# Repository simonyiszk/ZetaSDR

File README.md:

# ZetaSDR
ZetaSDR HF rádióvevő extra funkciókkal kiegészítve (PLL, USB hangkártya)

Fejlesztői környezet: [https://github.com/Community-PIO-CH32V/platform-ch32v](https://github.com/Community-PIO-CH32V/platform-ch32v).\
Az elektronikai terveket [KiCad](https://www.kicad.org/) seítségével készítettem.

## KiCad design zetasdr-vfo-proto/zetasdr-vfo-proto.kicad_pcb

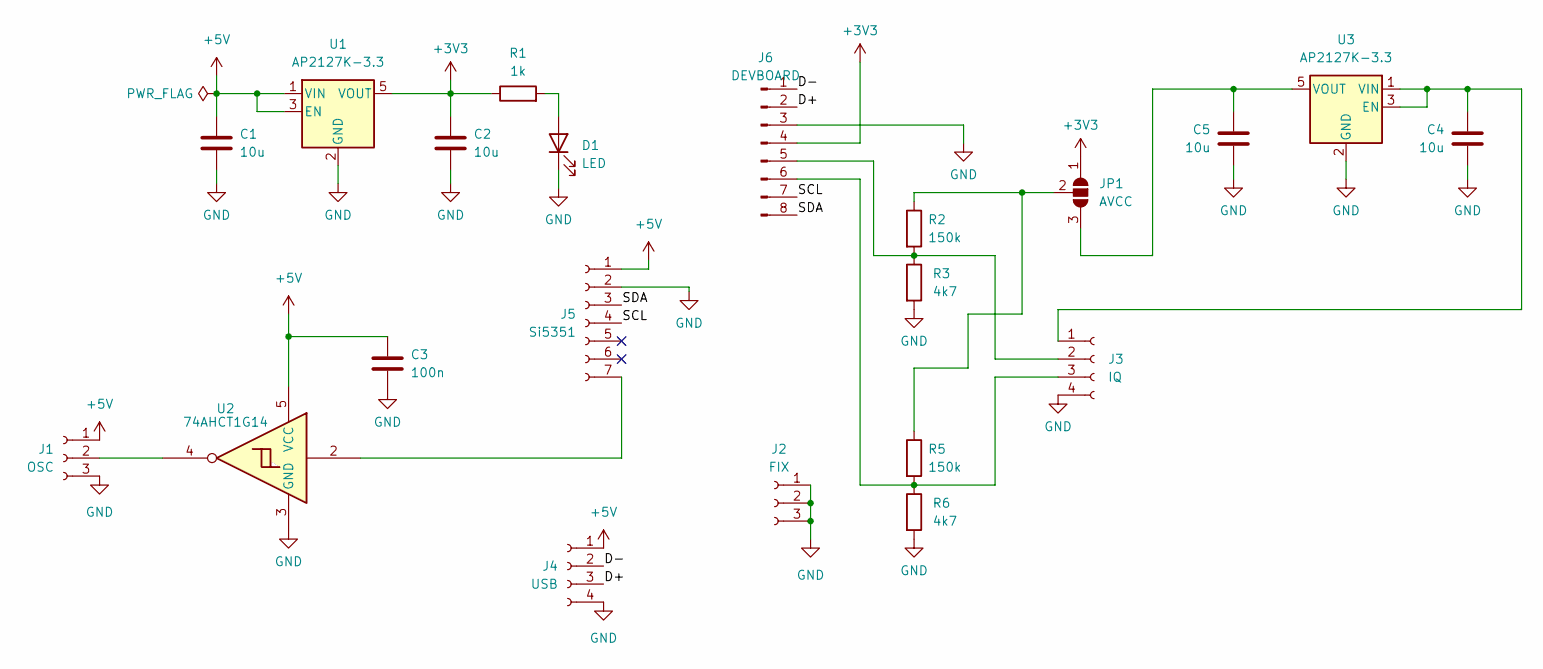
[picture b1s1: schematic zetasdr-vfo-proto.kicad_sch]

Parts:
C1, C2, C4, C5: 10u; C_0805_2012Metric_Pad1.18x1.45mm_HandSolder
C3: 100n; C_0805_2012Metric_Pad1.18x1.45mm_HandSolder
D1: LED; LED_0805_2012Metric_Pad1.15x1.40mm_HandSolder
J1: OSC; PinSocket_1x03_P2.54mm_Vertical
J2: FIX; PinSocket_1x03_P2.54mm_Vertical
J3: IQ; PinSocket_1x04_P2.54mm_Vertical
J4: USB; PinSocket_1x04_P2.54mm_Vertical
J5: Si5351; PinSocket_1x07_P2.54mm_Horizontal
J6: DEVBOARD; PinHeader_1x08_P2.54mm_Vertical
JP1: AVCC; SolderJumper-3_P1.3mm_Open_RoundedPad1.0x1.5mm
R1: 1k; R_0805_2012Metric_Pad1.20x1.40mm_HandSolder
R2, R5: 150k; R_0805_2012Metric_Pad1.20x1.40mm_HandSolder
R3, R6: 4k7; R_0805_2012Metric_Pad1.20x1.40mm_HandSolder
U1, U3: AP2127K-3.3; SOT-23-5_HandSoldering
U2: 74AHCT1G14; SOT-23-5_HandSoldering

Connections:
+3V3: C2.1, J6.4, JP1.1 (A), R1.1, U1.5 (VOUT)
+5V: C1.1, C3.1, J1.1, J4.1, J5.1, U1.1 (VIN), U1.3 (EN), U2.5 (VCC)
/D+: J4.3, J6.2
/D-: J4.2, J6.1
/SCL: J5.4, J6.7
/SDA: J5.3, J6.8
GND: C1.2, C2.2, C3.2, C4.2, C5.2, D1.1 (K), J1.3, J2.1, J2.2, J2.3, J3.4, J4.4, J5.2, J6.3, R3.2, R6.2, U1.2 (GND), U2.3 (GND), U3.2 (GND)
unnamed: D1.2 (A), R1.2
unnamed: J1.2, U2.4
unnamed: C4.1, J3.1, U3.1 (VIN), U3.3 (EN)
unnamed: J3.2, J6.5, R2.2, R3.1
unnamed: J3.3, J6.6, R5.2, R6.1
unnamed: J5.7, U2.2
unnamed: C5.1, JP1.3 (B), U3.5 (VOUT)
unnamed: JP1.2 (C), R2.1, R5.1

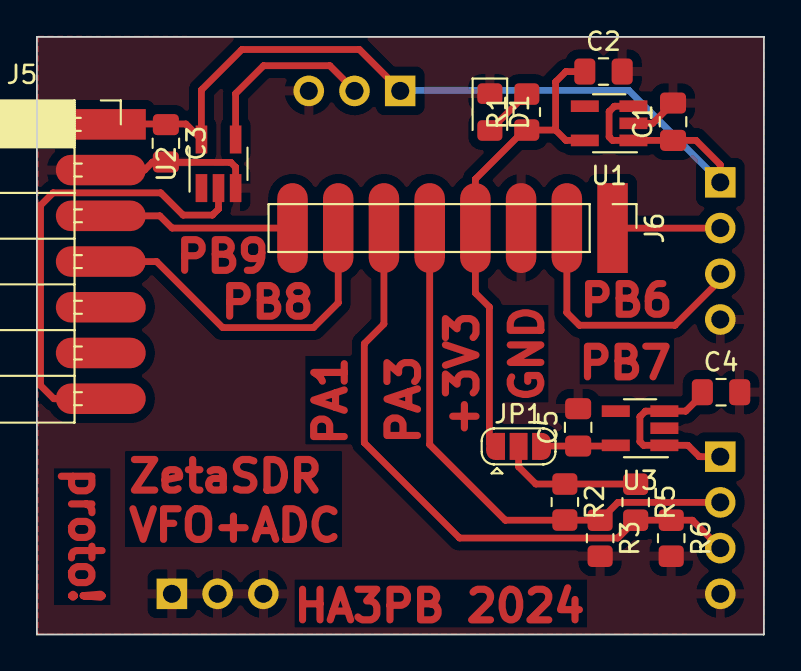
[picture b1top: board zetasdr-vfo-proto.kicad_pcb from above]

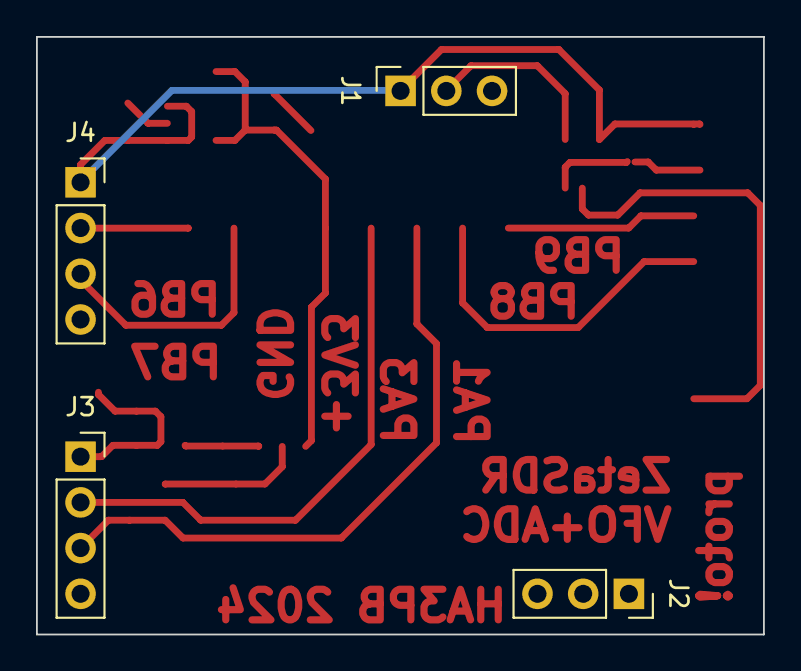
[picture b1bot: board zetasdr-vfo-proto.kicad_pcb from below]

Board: 2 copper layers, 40.4 x 33.2 mm, 21 parts (4 on the bottom side), 15 nets.

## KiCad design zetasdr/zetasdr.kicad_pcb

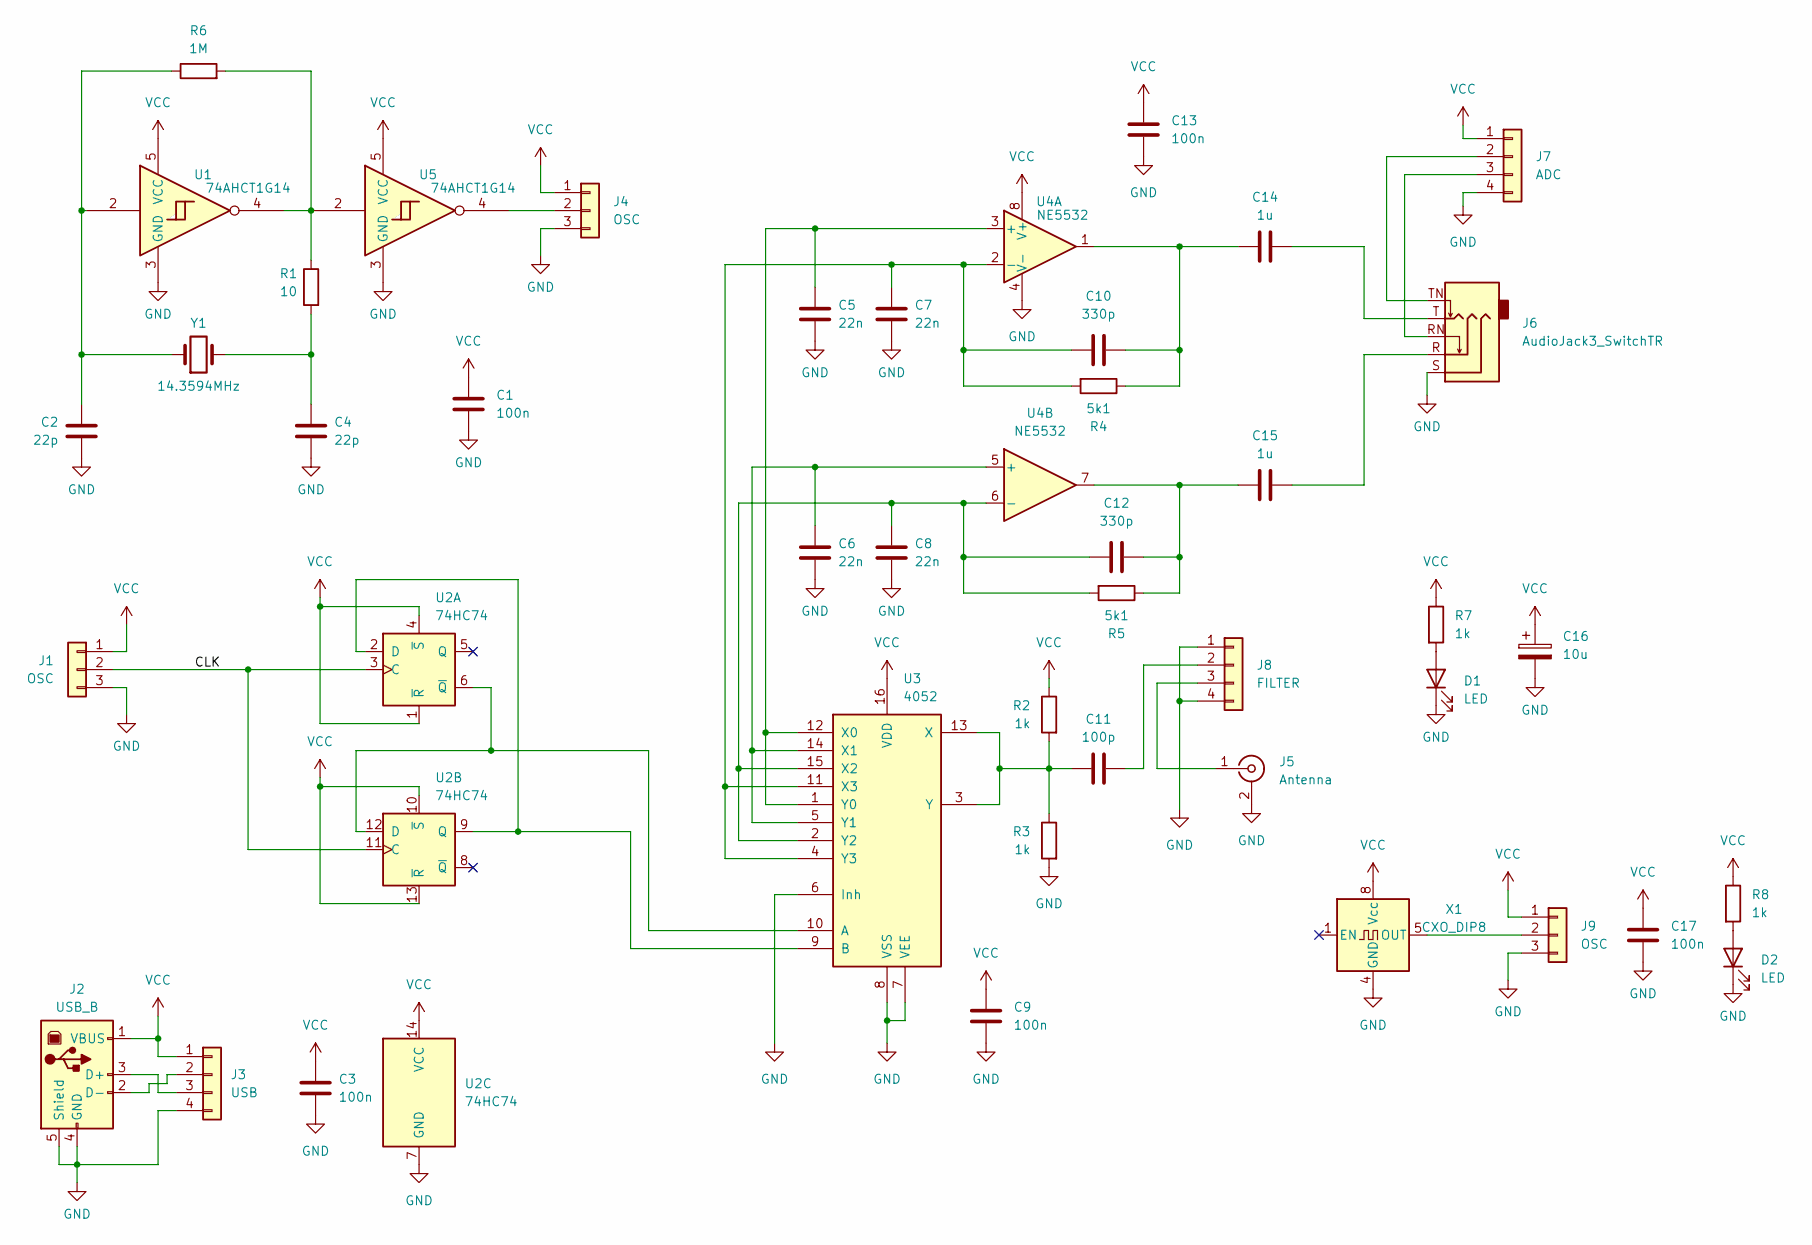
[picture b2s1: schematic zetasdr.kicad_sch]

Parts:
C1, C3, C9, C13, C17: 100n; C_0805_2012Metric_Pad1.18x1.45mm_HandSolder
C2, C4: 22p; C_0805_2012Metric_Pad1.18x1.45mm_HandSolder
C5, C6, C7, C8: 22n; C_Disc_D3.0mm_W1.6mm_P2.50mm
C10, C12: 330p; C_Disc_D3.0mm_W1.6mm_P2.50mm
C11: 100p; C_Disc_D3.0mm_W1.6mm_P2.50mm
C14, C15: 1u; C_0805_2012Metric_Pad1.18x1.45mm_HandSolder
C16: 10u; CP_Radial_D5.0mm_P2.50mm
D1: LED; LED_D3.0mm
D2: LED; LED_0805_2012Metric_Pad1.15x1.40mm_HandSolder
J1: OSC; PinHeader_1x03_P2.54mm_Vertical
J2: USB_B; USB_B_Lumberg_2411_02_Horizontal
J3: USB; PinHeader_1x04_P2.54mm_Vertical
J4, J9: OSC; PinSocket_1x03_P2.54mm_Vertical
J5: Antenna; SMA_Amphenol_901-143_Horizontal
J6: AudioJack3_SwitchTR; Jack_3.5mm_CUI_SJ1-3525N_Horizontal
J7: ADC; PinHeader_1x04_P2.54mm_Vertical
J8: FILTER; PinHeader_1x04_P2.54mm_Vertical
R1: 10; R_0805_2012Metric_Pad1.20x1.40mm_HandSolder
R2, R3: 1k; R_Axial_DIN0204_L3.6mm_D1.6mm_P5.08mm_Horizontal
R4, R5: 5k1; R_Axial_DIN0204_L3.6mm_D1.6mm_P5.08mm_Horizontal
R6: 1M; R_0805_2012Metric_Pad1.20x1.40mm_HandSolder
R7, R8: 1k; R_0805_2012Metric_Pad1.20x1.40mm_HandSolder
U1, U5: 74AHCT1G14; SOT-23-5
U2: 74HC74; DIP-14_W7.62mm_Socket_LongPads
U3: 4052; DIP-16_W7.62mm_Socket_LongPads
U4: NE5532; DIP-8_W7.62mm_Socket_LongPads
X1: CXO_DIP8; Oscillator_DIP-8
Y1: 14.3594MHz; Crystal_HC49-4H_Vertical

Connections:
/CLK: J1.2, U2.3 (C), U2.11 (C)
GND: C1.2, C2.2, C3.2, C4.2, C5.2, C6.2, C7.2, C8.2, C9.1, C13.1, C16.2, C17.2, D1.1 (K), D2.1 (K), J1.3, J2.4 (GND), J2.5 (Shield), J3.4, J4.3, J5.2 (Ext), J6.S, J7.4, J8.1, J8.4, J9.3, R3.2, U1.3 (GND), U2.7 (GND), U3.6 (Inh), U3.7 (VEE), U3.8 (VSS), U4.4 (V-), U5.3 (GND), X1.4 (GND)
unnamed: C2.1, R6.1, U1.2, Y1.1
unnamed: C4.1, R1.2, Y1.2
unnamed: C10.2, C14.1, R4.1, U4.1
unnamed: C12.2, C15.1, R5.1, U4.7
unnamed: C14.2, J6.T
unnamed: C15.2, J6.R
unnamed: D1.2 (A), R7.2
unnamed: D2.2 (A), R8.2
unnamed: J2.3 (D+), J3.3
unnamed: J2.2 (D-), J3.2
unnamed: J4.2, U5.4
unnamed: J5.1 (In), J8.3
unnamed: J6.TN, J7.2
unnamed: J6.RN, J7.3
unnamed: C11.2, J8.2
unnamed: J9.2, X1.5 (OUT)
unnamed: R1.1, R6.2, U1.4, U5.2
unnamed: U2.2 (D), U2.9 (Q), U3.9 (B)
unnamed: U2.6 (~Q), U2.12 (D), U3.10 (A)
unnamed: C5.1, U3.1 (Y0), U3.12 (X0), U4.3 (+)
unnamed: C6.1, U3.5 (Y1), U3.14 (X1), U4.5 (+)
unnamed: C8.1, C12.1, R5.2, U3.2 (Y2), U3.15 (X2), U4.6 (-)
unnamed: C7.1, C10.1, R4.2, U3.4 (Y3), U3.11 (X3), U4.2 (-)
unnamed: C11.1, R2.2, R3.1, U3.3 (Y), U3.13 (X)
VCC: C1.1, C3.1, C9.2, C13.2, C16.1, C17.1, J1.1, J2.1 (VBUS), J3.1, J4.1, J7.1, J9.1, R2.1, R7.1, R8.1, U1.5 (VCC), U2.1 (~R), U2.4 (~S), U2.10 (~S), U2.13 (~R), U2.14 (VCC), U3.16 (VDD), U4.8 (V+), U5.5 (VCC), X1.8 (Vcc)

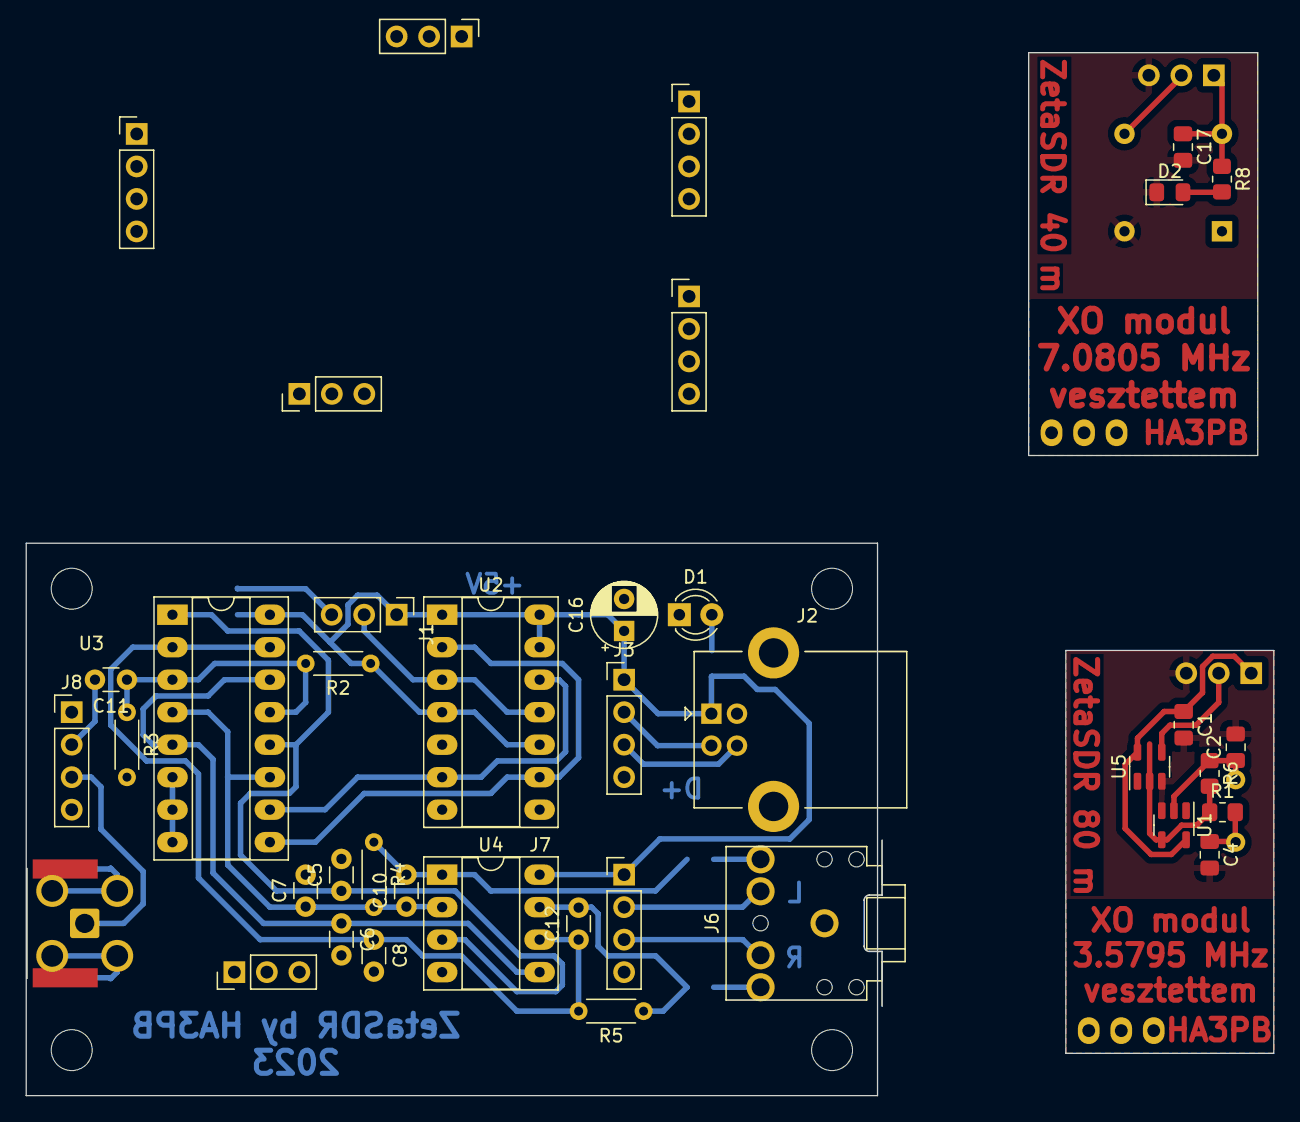
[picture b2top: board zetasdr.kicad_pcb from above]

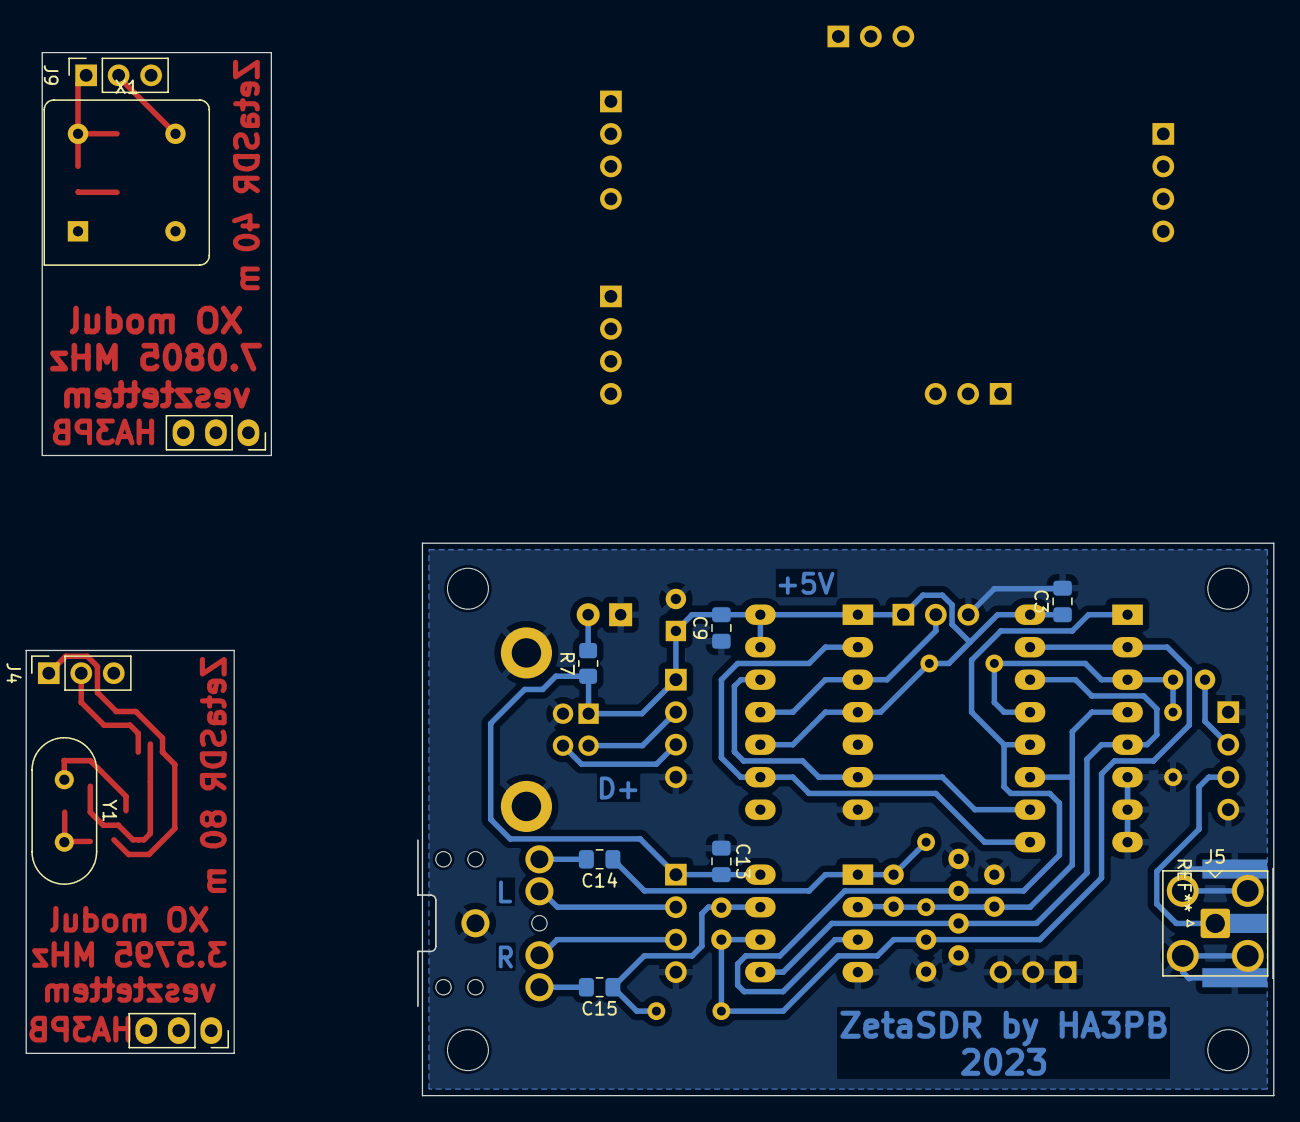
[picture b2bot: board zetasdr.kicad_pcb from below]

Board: 2 copper layers, 97.5 x 81.5 mm, 47 parts (11 on the bottom side), 27 nets.

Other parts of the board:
J?: ADC; PinHeader_1x04_P2.54mm_Vertical
J?#2: USB; PinHeader_1x04_P2.54mm_Vertical
J?#3: FILTER; PinHeader_1x04_P2.54mm_Vertical
J?#4: OSC; PinHeader_1x03_P2.54mm_Vertical

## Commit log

2023-10-15 Add schematic and pcb design
2023-10-15 Add sound card firmware for CH32V203 eval board
2024-03-17 Add fancy BOM
2024-03-17 Add firmware
    Composite USB device w/ stereo analog input & virtual serial port.
    Features:
    192kHz 12-bit stereo ADC IN.
    Composite USB device with unique yet standard hand-made descriptor.
    Center frequency can be set via serial port (desired value is being set by configuring an Si5351 VFO via I2C)
    DC removal digital IIR filter implemented using fixed-point arithmetic.
2024-03-17 Add rigctl tuning script
    Interface between the ZetaSDR and the SDR++ software.
    The set frequency in the software is being sent to the HW via rigctl (TCP) and serial port.
2024-09-20 Add basic vfo shield
2024-09-21 Add adapter board for vfo shield testing purposes
2025-01-03 Basic firmware for STM32
    Tested on a STM32 Redpill board (https://github.com/simonyiszk/STM32-RedPill).
    Generate code in CubeMX to obtain CMSIS and HAL Drivers & Clone tinyusb repository(https://github.com/hathach/tinyusb) into Libs folder to get everything working
